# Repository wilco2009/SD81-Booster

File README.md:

# SD81 Booster — SD, sound, voice and memory interface for ZX81

An open hardware, open source project packing many features in a single interface.

## Credits

```
Hardware design & MCU firmware:  Alejandro Valero (wilco2009)
Z80 code / Modified ROM:         Pedro Gimeno (pgimeno)

Based on ZX81 ROM disassembly by Geoff Wearmouth
Preserved by Tomaž Šolc (https://www.tablix.org/~avian/spectrum/rom/)
```

## Features

- Load and save programs from/to a FAT32 microSD card in `.P` format, supporting common file and directory operations: list directory, copy/move/rename/delete files, change/create/remove directories.
- Up to 512 KB RAM, using a memory mapper in 8 KB blocks. There's also a simplified mode that allows up to 256 KB RAM, needing very simple paging code.
- The selected mapper page for any given block can be read back.
- Up to 128 user-defined characters. Compatible with the QuickSilva character definition mode — no longer restricted to the ROM's 64 characters and their inverses.
- AY-3-8910/12 sound chip emulation with `PLAY` command.
- AY VGM player, plays in background (does not support VGMs containing other chips than the AY).
- AY sound effects in background, via a programmable virtual machine (PEG).
- Speech synthesis based on the SP0256 chip (General Instrument), the same synthesiser used by the Currah MicroSpeech (ZX Spectrum) and The Voice (Videopac G7000/Odyssey 2). The `LOAD *SAY` command accepts English text directly.
- WAV audio file playback (uncompressed PCM).
- RGB colour video output, compatible with the Chroma81 interface standard.
- Real-time clock (RTC) with CR2032 backup battery.
- Programmable DB9 joystick port.
- Possibility to run code in the region between 32K and 48K (MC45 mode — see below).
- Minimal changes to the standard ROM. In particular, the ZX Printer and tape routines are preserved intact.

### What it doesn't do

- File names are restricted to characters supported by the ZX81 keyboard. The permitted characters for filenames are `A`–`Z`, `0`–`9`, `.`, `,`, `;`, `$`, `(`, `)`, `=`, `+`, `-`. The `/` character is the directory separator. Letters are treated as upper case when saving.
- AY sound chip emulation is not cycle-accurate.
- AY sound chip register access is not compatible with other interfaces.
- The memory mapping I/O port and layout are not compatible with other interfaces.
- There are no new BASIC keywords; most new functions are implemented through extensions to the `LOAD` and `SAVE` commands.

### Possible compatibility issues

- The SD81 Booster incorporates the functionality of the Chroma81 (RGB colour video) and QuickSilva (128 user-defined characters) interfaces. It is not designed to be used simultaneously with those physical interfaces connected at the same time.
- The memory area between 8 KB and 16 KB is no longer a mirror of the area between 0 and 8 KB.
- The same area is now read/write rather than read-only. If a program writes to used areas within that space, the expanded commands may crash and a hardware reset will be necessary.
- The ROM changes 8 bytes with respect to the original. Programs that depend on those specific bytes may fail (considered highly unlikely in practice).
- The memory mapper I/O port may clash with that of other interfaces.
- The general command interface I/O ports might clash with those of other interfaces.
- The USB-C port uses a CH340G chip for serial console output (115200-8N1). In Spectrum mode, port FBh is used, which is incompatible with the ZX Printer.

## MC45

MC45 (Machine Code in blocks 4 and 5) is a mode that allows any Z80 instruction — not just those with opcodes in the ranges 40h–7Fh and C0h–FFh — to run in the address range 8000h–BFFFh. The drawback is that the display file can no longer be in that area, so BASIC programs larger than 16 KB cannot be loaded or written while this mode is active.

The interface already includes a 33Ω protective resistor on the /HALT line internally. No modification to the ZX81 is required. There is no jumper to disable this feature on the current hardware version.

> **Note:** Some older documentation refers to a 680Ω resistor — that value applies to an alternative ZX81 hardware modification, not to the SD81 Booster itself.

## Getting started

The **SYS** folder must be present in the root of the microSD card — without it the interface will not start. It contains the ROM files required for operation.

See [MANUAL/ES/SD81_Manual_ES.md](MANUAL/ES/SD81_Manual_ES.md) for the full user manual in Spanish.

For the technical reference and MCU command descriptions, see the [DOC folder](DOC/).

## Firmware update

**Normal update (via SD bootloader):**
1. Copy the firmware `.bin` file (renamed as `firmware.bin`) to the root of the SD card.
2. Power on the ZX81. The bootloader detects the file, flashes it at `0x0800C000`, deletes it, and boots the application.

**Emergency recovery (via USB, for advanced users):**
1. Open the interface case and bridge the two upper pins of jumper **JP7** (on the component side, next to the USB-C port).
2. Connect the USB-C cable to a PC.
3. Use **STM32CubeProgrammer** to flash:
   - Bootloader at `0x08000000`
   - Application at `0x0800C000`

See [FIRMWARE/README_update.md](FIRMWARE/README_update.md) for detailed instructions.

## Building the ZX81 ROM

The ROM listing used here is the disassembly work of [Geoff Wearmouth](http://web.archive.org/web/20150815035607/http://www.wearmouth.demon.co.uk/zx81.htm), preserved by [Tomaž Šolc](https://www.tablix.org/~avian/spectrum/rom/).

The ROM can be built using [GNU binutils for Z80](https://github.com/atsidaev/binutils-z80), [Pasmo](https://pasmo.speccy.org/) or [MDL](https://github.com/santiontanon/mdlz80optimizer).

To build with GNU binutils:

    z80-unknown-coff-as sdmodrom.asm -o sdmodrom.o
    z80-unknown-coff-ld -Ttext 0 sdmodrom.o -o sdmodrom.bin

To build with Pasmo:

    pasmo sdmodrom.asm sdmodrom.bin

To build with MDL (dialects `pasmo` or `macro80`):

    java -jar mdl.jar -dialect macro80 -bin sdmodrom.bin sdmodrom.asm

## Games and game engines

Games and engines written for, or ported to, the SD81 Booster. Each one lives in its own repository:

- [Space Invaders](https://github.com/wilco2009/SD81Invaders): a replica of Taito's 1978 arcade, written from scratch in Z80 and tested on real hardware.
- [Manic Miner](https://codeberg.org/wilco2009/manicsd81): port of the ZX Spectrum classic (work in progress).
- [NanacoHell](https://codeberg.org/wilco2009/NANAKOHell_SD81Booster): port of the Spectrum 128K game, running in the Spectrum-compatible HiRes mode.
- [Mario](https://github.com/wilco2009/sd81mario): a Mario platformer.
- [ZXOilPanic](https://github.com/wilco2009/ZXOilPanic): a Game & Watch style oil-panic game, with an extra build target for the ZX81 + SD81 Booster.
- [SCUMM and AGI interpreters](https://github.com/wilco2009/SCUMM): interpreters running on the ZX81's Z80, for SCUMM v2 (Maniac Mansion, Zak McKracken) and Sierra's AGI (Space Quest I first).

The two-player network games (Connect 4, chess, Scrabble and the real-time sports games) are part of this repository, in [`EXAMPLES/NETGAME`](EXAMPLES/NETGAME).

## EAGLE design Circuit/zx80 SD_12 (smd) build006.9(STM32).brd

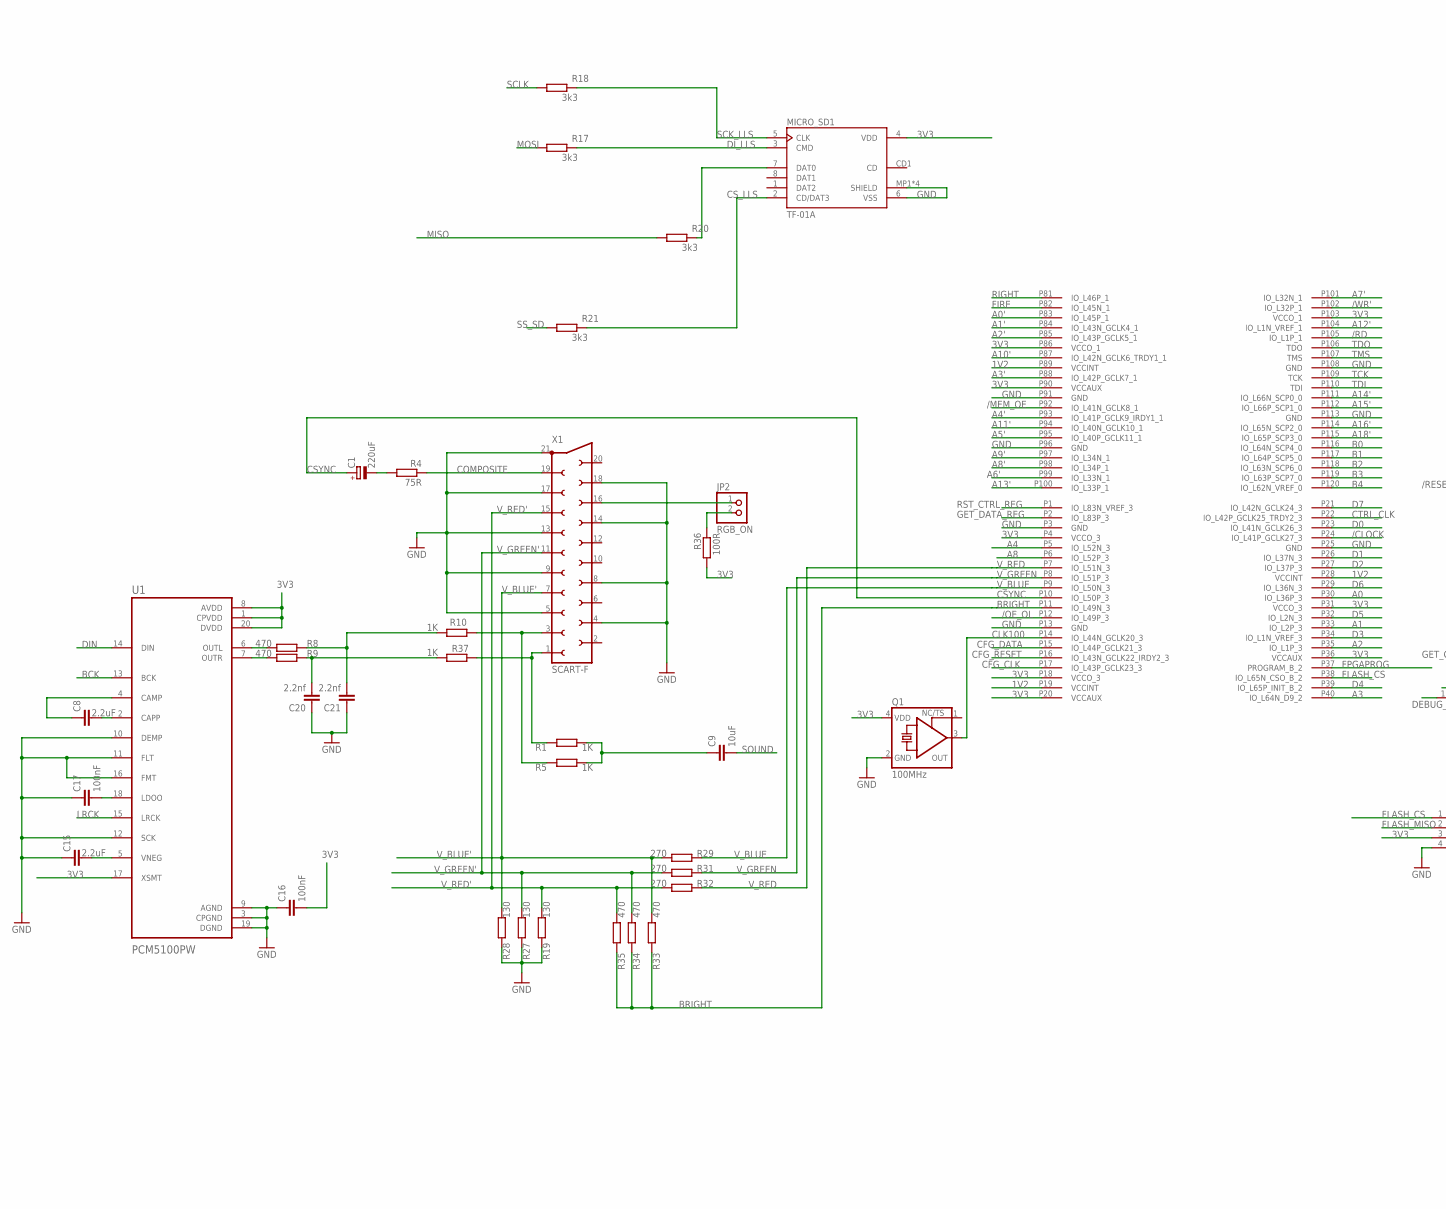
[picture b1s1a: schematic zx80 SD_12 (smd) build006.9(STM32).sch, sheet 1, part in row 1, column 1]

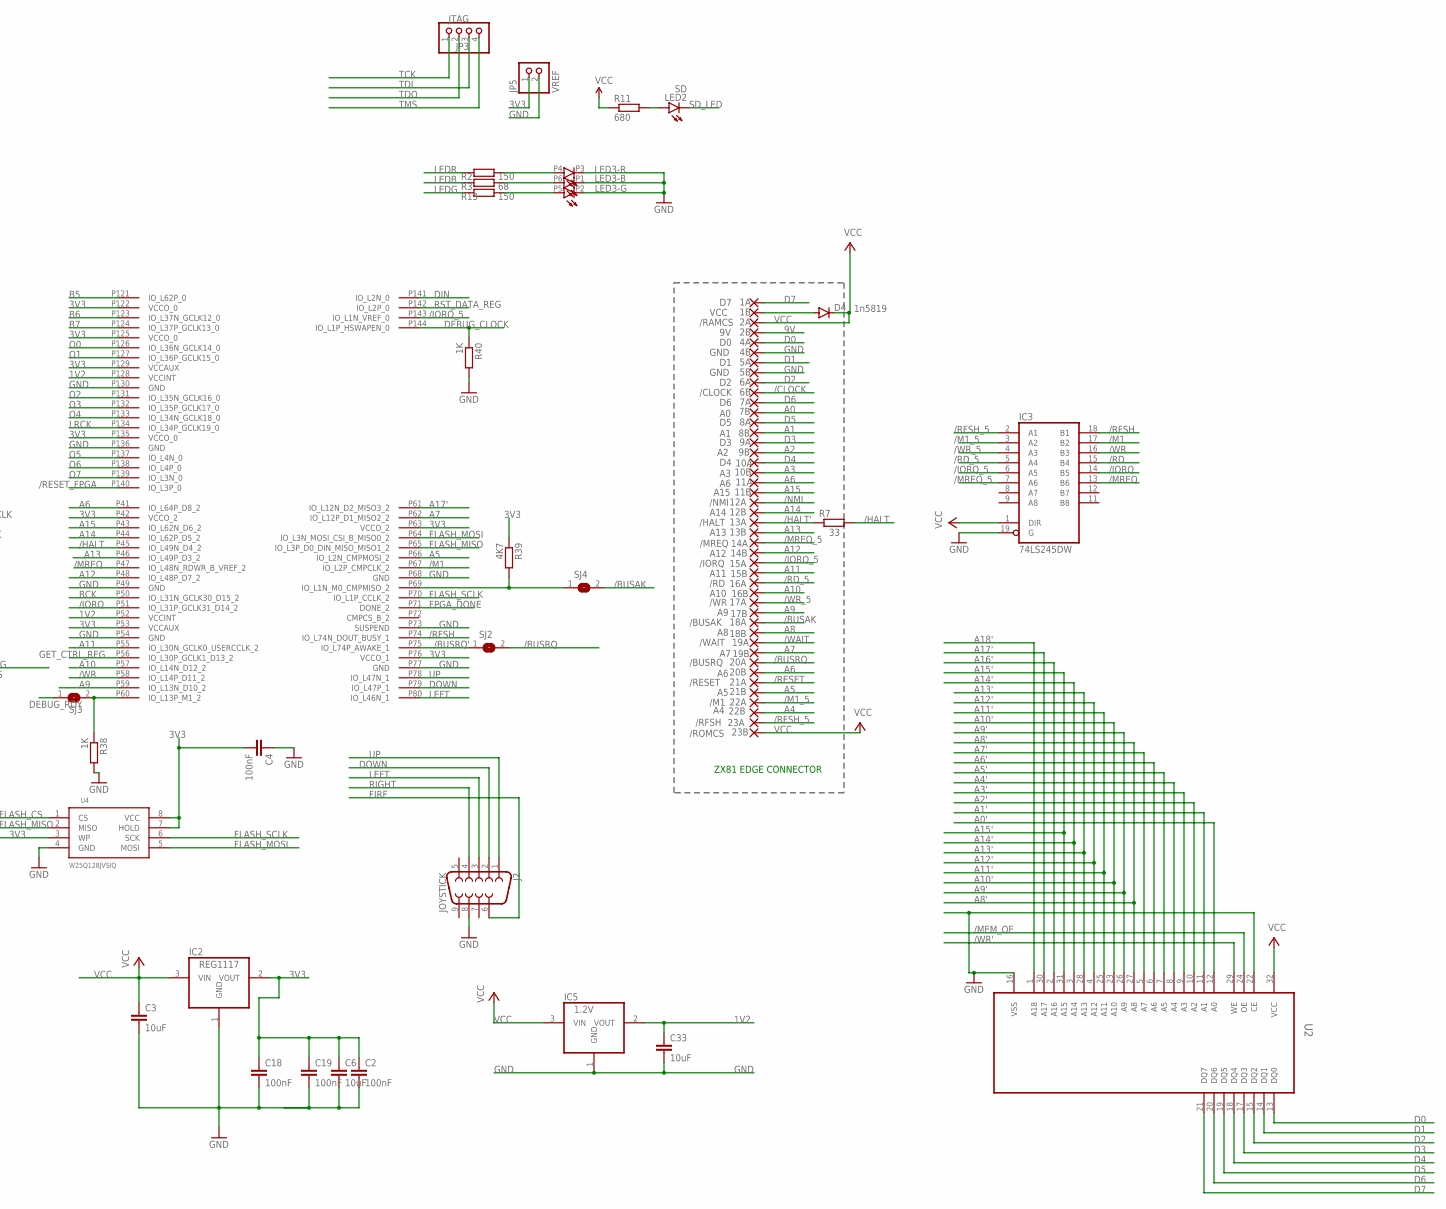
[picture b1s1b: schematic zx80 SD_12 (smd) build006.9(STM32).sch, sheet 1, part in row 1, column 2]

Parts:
1A: D7; EDGEPIN
1B: VCC; EDGEPIN
2A: /RAMCS; EDGEPIN
2B: 9V; EDGEPIN
4A: D0; EDGEPIN
4B, 5B: GND; EDGEPIN
5A: D1; EDGEPIN
6A: D2; EDGEPIN
6B: /CLOCK; EDGEPIN
7A: D6; EDGEPIN
7B: A0; EDGEPIN
8A: D5; EDGEPIN
8B: A1; EDGEPIN
9A: D3; EDGEPIN
9B: A2; EDGEPIN
10A: D4; EDGEPIN
10B: A3; EDGEPIN
11A, 20B: A6; EDGEPIN
11B: A15; EDGEPIN
12A: /NMI; EDGEPIN
12B: A14; EDGEPIN
13A: /HALT; EDGEPIN
13B: A13; EDGEPIN
14A: /MREQ; EDGEPIN
14B: A12; EDGEPIN
15A: /IORQ; EDGEPIN
15B: A11; EDGEPIN
16A: /RD; EDGEPIN
16B: A10; EDGEPIN
17A: /WR; EDGEPIN
17B: A9; EDGEPIN
18A: /BUSAK; EDGEPIN
18B: A8; EDGEPIN
19A: /WAIT; EDGEPIN
19B: A7; EDGEPIN
20A: /BUSRQ; EDGEPIN
21A: /RESET; EDGEPIN
21B: A5; EDGEPIN
22A: /M1; EDGEPIN
22B: A4; EDGEPIN
23A: /RFSH; EDGEPIN
23B: /ROMCS; EDGEPIN
C1: 220uF; UD-6,3X7,7_NICHICON
C2, C4, C16, C17, C18, C19: 100nF; C0402K
C3, C6, C9, C33: 10uF; C0402K
C8, C15: 2.2uF; C0402K
C20, C21: 2.2nf; C0603K
D4: 1n5819; SOD323-W
IC2: REG1117; SOT223
IC3: 74LS245DW; SO20W
IC5: 1.2V; SOT223
J2: JOYSTICK; DB9_MALE
JP2: RGB_ON; 1X02
JP3: JTAG; 1X04
JP5: VREF; 1X02
LED2: SD; CHIPLED_0805
LED3: STATUS; 3535-PLCC6
MICRO_SD1: TF-01A
Q1: 100MHz; 3.2X2.5_KXO-V96
R1, R5, R10, R37, R38, R40: 1K; R0402
R2, R13: 150; R0402
R3: 68; R0402
R4: 75R; R0402
R7: 33; R0402
R8, R9, R33, R34, R35: 470; R0402
R11: 680; R0402
R17, R18, R20, R21: 3k3; R0402
R19, R27, R28: 130; R0402
R29, R31, R32: 270; R0402
R36: 100R; R0402
R39: 4K7; R0402
SJ2, SJ3, SJ4: SJ
U1: PCM5100PW; SOP65P640X120-20N
U2: AS6C4008; SOP32-5
U4: W25Q128JVSIQ; SO08-EIAJ
U6: XC6SLX9-2TQG144C; TQ144
X1: SCART-F

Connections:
1V2: C33.1, IC5.2 (VOUT), U6.P19 (VCCINT), U6.P28 (VCCINT), U6.P52 (VCCINT), U6.P89 (VCCINT), U6.P128 (VCCINT)
3V3: C2.1, C4.2, C6.1, C16.2, C18.1, C19.1, IC2.2 (VOUT), JP5.1, MICRO_SD1.4 (VDD), Q1.4 (VDD), R36.2, R39.1, U1.1 (CPVDD), U1.8 (AVDD), U1.17 (XSMT), U1.20 (DVDD), U4.3 (WP), U4.7 (HOLD), U4.8 (VCC), U6.P4 (VCCO_3), U6.P18 (VCCO_3), U6.P20 (VCCAUX), U6.P31 (VCCO_3), U6.P36 (VCCAUX), U6.P42 (VCCO_2), U6.P53 (VCCAUX), U6.P63 (VCCO_2), U6.P76 (VCCO_1), U6.P86 (VCCO_1), U6.P90 (VCCAUX), U6.P103 (VCCO_1), U6.P122 (VCCO_0), U6.P125 (VCCO_0), U6.P129 (VCCAUX), U6.P135 (VCCO_0); also elsewhere on the board
9V: 2B.1
/BUSAK: 18A.1, SJ4.2
/BUSRQ: 20A.1, SJ2.2
/BUSRQ': SJ2.1, U6.P75 (IO_L74P_AWAKE_1)
/CLOCK: 6B.1, U6.P24 (IO_L41P_GCLK27_3)
/HALT: R7.2, U6.P45 (IO_L49N_D4_2)
/HALT': 13A.1, R7.1
/IORQ: IC3.14 (B5), U6.P51 (IO_L31P_GCLK31_D14_2)
/IORQ_5: 15A.1, IC3.6 (A5), U6.P143 (IO_L1N_VREF_0)
/M1: IC3.17 (B2), U6.P67 (IO_L2P_CMPCLK_2)
/M1_5: 22A.1, IC3.3 (A2)
/MEM_OE: U2.24 (OE), U6.P92 (IO_L41N_GCLK8_1); also elsewhere on the board
/MREQ: IC3.13 (B6), U6.P47 (IO_L48N_RDWR_B_VREF_2)
/MREQ_5: 14A.1, IC3.7 (A6)
/NMI: 12A.1
/OE_OL: U6.P12 (IO_L49P_3); also elsewhere on the board
/RD: IC3.15 (B4), U6.P105 (IO_L1P_1)
/RD_5: 16A.1, IC3.5 (A4)
/RESET: 21A.1; also elsewhere on the board
/RESET_FPGA: U6.P140 (IO_L3P_0); also elsewhere on the board
/RFSH: IC3.18 (B1), U6.P74 (IO_L74N_DOUT_BUSY_1)
/RFSH_5: 23A.1, IC3.2 (A1)
/WAIT: 19A.1; also elsewhere on the board
/WR: IC3.16 (B3), U6.P58 (IO_L14P_D11_2)
/WR': U2.29 (WE), U6.P102 (IO_L32P_1); also elsewhere on the board
/WR_5: 17A.1, IC3.4 (A3)
A0: 7B.1, U6.P30 (IO_L36P_3)
A0': U2.12 (A0), U6.P83 (IO_L45P_1); also elsewhere on the board
A1: 8B.1, U6.P33 (IO_L2P_3)
A1': U2.11 (A1), U6.P84 (IO_L43N_GCLK4_1); also elsewhere on the board
A2: 9B.1, U6.P35 (IO_L1P_3)
A2': U2.10 (A2), U6.P85 (IO_L43P_GCLK5_1); also elsewhere on the board
A3: 10B.1, U6.P40 (IO_L64N_D9_2)
A3': U2.9 (A3), U6.P88 (IO_L42P_GCLK7_1); also elsewhere on the board
A4: 22B.1, U6.P5 (IO_L52N_3)
A4': U2.8 (A4), U6.P93 (IO_L41P_GCLK9_IRDY1_1); also elsewhere on the board
A5: 21B.1, U6.P66 (IO_L2N_CMPMOSI_2)
A5': U2.7 (A5), U6.P95 (IO_L40P_GCLK11_1); also elsewhere on the board
A6: 11A.1, 20B.1, U6.P41 (IO_L64P_D8_2)
A6': U2.6 (A6), U6.P99 (IO_L33N_1); also elsewhere on the board
A7: 19B.1, U6.P62 (IO_L12P_D1_MISO2_2)
A7': U2.5 (A7), U6.P101 (IO_L32N_1); also elsewhere on the board
A8: 18B.1, U6.P6 (IO_L52P_3)
A8': U2.27 (A8), U6.P98 (IO_L34P_1); also elsewhere on the board
A9: 17B.1, U6.P59 (IO_L13N_D10_2)
A9': U2.26 (A9), U6.P97 (IO_L34N_1); also elsewhere on the board
A10: 16B.1, U6.P57 (IO_L14N_D12_2)
A10': U2.23 (A10), U6.P87 (IO_L42N_GCLK6_TRDY1_1); also elsewhere on the board
A11: 15B.1, U6.P55 (IO_L30N_GCLK0_USERCCLK_2)
A11': U2.25 (A11), U6.P94 (IO_L40N_GCLK10_1); also elsewhere on the board
A12: 14B.1, U6.P48 (IO_L48P_D7_2)
A12': U2.4 (A12), U6.P104 (IO_L1N_VREF_1); also elsewhere on the board
A13: 13B.1, U6.P46 (IO_L49P_D3_2)
A13': U2.28 (A13), U6.P100 (IO_L33P_1); also elsewhere on the board
A14: 12B.1, U6.P44 (IO_L62P_D5_2)
A14': U2.3 (A14), U6.P111 (IO_L66N_SCP0_0); also elsewhere on the board
A15: 11B.1, U6.P43 (IO_L62N_D6_2)
A15': U2.31 (A15), U6.P112 (IO_L66P_SCP1_0); also elsewhere on the board
A16': U2.2 (A16), U6.P114 (IO_L65N_SCP2_0); also elsewhere on the board
A17': U2.30 (A17), U6.P61 (IO_L12N_D2_MISO3_2); also elsewhere on the board
A18': U2.1 (A18), U6.P115 (IO_L65P_SCP3_0); also elsewhere on the board
B0: U6.P116 (IO_L64N_SCP4_0); also elsewhere on the board
B1: U6.P117 (IO_L64P_SCP5_0); also elsewhere on the board
B2: U6.P118 (IO_L63N_SCP6_0); also elsewhere on the board
B3: U6.P119 (IO_L63P_SCP7_0); also elsewhere on the board
B4: U6.P120 (IO_L62N_VREF_0); also elsewhere on the board
B5: U6.P121 (IO_L62P_0); also elsewhere on the board
B6: U6.P123 (IO_L37N_GCLK12_0); also elsewhere on the board
B7: U6.P124 (IO_L37P_GCLK13_0); also elsewhere on the board
BCK: U1.13 (BCK), U6.P50 (IO_L31N_GCLK30_D15_2)
BRIGHT: R33.1, R34.1, R35.1, U6.P11 (IO_L49N_3)
CFG_CLK: U6.P17 (IO_L43P_GCLK23_3); also elsewhere on the board
CFG_DATA: U6.P15 (IO_L44P_GCLK21_3); also elsewhere on the board
CFG_RESET: U6.P16 (IO_L43N_GCLK22_IRDY2_3); also elsewhere on the board
CLK100: Q1.3 (OUT), U6.P14 (IO_L44N_GCLK20_3)
COMPOSITE: R4.1, X1.19
CSYNC: C1.+, U6.P10 (IO_L50P_3)
CS_LLS: MICRO_SD1.2 (CD/DAT3), R21.2
CTRL_CLK: U6.P22 (IO_L42P_GCLK25_TRDY2_3); also elsewhere on the board
D0: 4A.1, U2.13 (DQ0), U6.P23 (IO_L41N_GCLK26_3)
D1: 5A.1, U2.14 (DQ1), U6.P26 (IO_L37N_3)
D2: 6A.1, U2.15 (DQ2), U6.P27 (IO_L37P_3)
D3: 9A.1, U2.17 (DQ3), U6.P34 (IO_L1N_VREF_3)
D4: 10A.1, U2.18 (DQ4), U6.P39 (IO_L65P_INIT_B_2)
D5: 8A.1, U2.19 (DQ5), U6.P32 (IO_L2N_3)
D6: 7A.1, U2.20 (DQ6), U6.P29 (IO_L36N_3)
D7: 1A.1, U2.21 (DQ7), U6.P21 (IO_L42N_GCLK24_3)
DEBUG_CLOCK: R40.1, U6.P144 (IO_L1P_HSWAPEN_0); also elsewhere on the board
DEBUG_RDY: SJ3.1; also elsewhere on the board
DIN: U1.14 (DIN), U6.P141 (IO_L2N_0)
DI_LLS: MICRO_SD1.3 (CMD), R17.2
DOWN: J2.2, U6.P79 (IO_L47P_1)
FIRE: J2.6, U6.P82 (IO_L45N_1)
FLASH_CS: U4.1 (CS), U6.P38 (IO_L65N_CSO_B_2); also elsewhere on the board
FLASH_MISO: U4.2 (MISO), U6.P65 (IO_L3P_D0_DIN_MISO_MISO1_2); also elsewhere on the board
FLASH_MOSI: U4.5 (MOSI), U6.P64 (IO_L3N_MOSI_CSI_B_MISO0_2); also elsewhere on the board
FLASH_SCLK: U4.6 (SCK), U6.P70 (IO_L1P_CCLK_2); also elsewhere on the board
FPGAPROG: U6.P37 (PROGRAM_B_2); also elsewhere on the board
FPGA_DONE: U6.P71 (DONE_2); also elsewhere on the board
GET_CTRL_REG: U6.P56 (IO_L30P_GCLK1_D13_2); also elsewhere on the board
GET_DATA_REG: U6.P2 (IO_L83P_3); also elsewhere on the board
GND: 4B.1, 5B.1, C2.2, C3.2, C4.1, C6.2, C15.1, C16.1, C17.1, C18.2, C19.2, C20.1, C21.1, C33.2, IC2.1 (GND), IC3.10 (GND), IC3.19 (G), IC5.1 (GND), J2.8, JP5.2, LED3.P1 (C), LED3.P2 (C), LED3.P3 (C), MICRO_SD1.6 (VSS), MICRO_SD1.MP1 (SHIELD), MICRO_SD1.MP2 (SHIELD), MICRO_SD1.MP3 (SHIELD), MICRO_SD1.MP4 (SHIELD), Q1.2 (GND), R19.2, R27.2, R28.2, R38.2, R40.2, U1.3 (CPGND), U1.9 (AGND), U1.10 (DEMP), U1.11 (FLT), U1.12 (SCK), U1.16 (FMT), U1.19 (DGND), U2.16 (VSS), U2.22 (CE), U4.4 (GND), U6.P3 (GND), U6.P13 (GND), U6.P25 (GND), U6.P49 (GND), U6.P54 (GND), U6.P68 (GND), U6.P73 (SUSPEND), U6.P77 (GND), U6.P91 (GND), U6.P96 (GND), U6.P108 (GND), U6.P113 (GND), U6.P130 (GND), U6.P136 (GND), X1.4, X1.5, X1.8, X1.9, X1.13, X1.14, X1.17, X1.18, X1.21; also elsewhere on the board
LEDB: R3.1; also elsewhere on the board
LEDG: R13.1; also elsewhere on the board
LEDR: R2.1; also elsewhere on the board
LEFT: J2.3, U6.P80 (IO_L46N_1)
LRCK: U1.15 (LRCK), U6.P134 (IO_L34P_GCLK19_0)
MISO: R20.1; also elsewhere on the board
MOSI: R17.1; also elsewhere on the board
unnamed: R39.2, SJ4.1, U6.P69 (IO_L1N_M0_CMPMISO_2)
unnamed: MICRO_SD1.7 (DAT0), R20.2
unnamed: 1B.1, D4.A
unnamed: C1.-, R4.2
unnamed: R5.1, R10.2, X1.3
unnamed: C9.1, R1.2, R5.2
unnamed: C21.2, R8.1, R10.1
unnamed: LED2.A, R11.2
unnamed: JP2.1, X1.16
unnamed: C20.2, R9.1, R37.1
unnamed: LED3.P4 (A), R2.2
unnamed: LED3.P6 (A), R3.2
unnamed: LED3.P5 (A), R13.2
unnamed: JP2.2, R36.1
unnamed: R38.1, SJ3.2, U6.P60 (IO_L13P_M1_2)
unnamed: R8.2, U1.6 (OUTL)
unnamed: R9.2, U1.7 (OUTR)
unnamed: C8.2, U1.2 (CAPP)
unnamed: C8.1, U1.4 (CAMP)
unnamed: C15.2, U1.5 (VNEG)
unnamed: C17.2, U1.18 (LDOO)
unnamed: R1.1, R37.2, X1.1
O0: U6.P126 (IO_L36N_GCLK14_0); also elsewhere on the board
O1: U6.P127 (IO_L36P_GCLK15_0); also elsewhere on the board
O2: U6.P131 (IO_L35N_GCLK16_0); also elsewhere on the board
O3: U6.P132 (IO_L35P_GCLK17_0); also elsewhere on the board
O4: U6.P133 (IO_L34N_GCLK18_0); also elsewhere on the board
O5: U6.P137 (IO_L4N_0); also elsewhere on the board
O6: U6.P138 (IO_L4P_0); also elsewhere on the board
O7: U6.P139 (IO_L3N_0); also elsewhere on the board
RIGHT: J2.4, U6.P81 (IO_L46P_1)
RST_CTRL_REG: U6.P1 (IO_L83N_VREF_3); also elsewhere on the board
RST_DATA_REG: U6.P142 (IO_L2P_0); also elsewhere on the board
SCK_LLS: MICRO_SD1.5 (CLK), R18.2
SCLK: R18.1; also elsewhere on the board
SD_LED: LED2.C; also elsewhere on the board
SOUND: C9.2; also elsewhere on the board
SS_SD: R21.1; also elsewhere on the board
TCK: JP3.1, U6.P109 (TCK)
TDI: JP3.3, U6.P110 (TDI)
TDO: JP3.2, U6.P106 (TDO)
TMS: JP3.4, U6.P107 (TMS)
UP: J2.1, U6.P78 (IO_L47N_1)
VCC: 2A.1, 23B.1, C3.1, D4.C, IC2.3 (VIN), IC3.1 (DIR), IC3.20 (VCC), IC5.3 (VIN), R11.1, U2.32 (VCC); also elsewhere on the board
V_BLUE: R29.1, U6.P9 (IO_L50N_3)
V_BLUE': R28.1, R29.2, R33.2, X1.7
V_GREEN: R31.1, U6.P8 (IO_L51P_3)
V_GREEN': R27.1, R31.2, R34.2, X1.11
V_RED: R32.1, U6.P7 (IO_L51N_3)
V_RED': R19.1, R32.2, R35.2, X1.15

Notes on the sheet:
ZX81 EDGE CONNECTOR

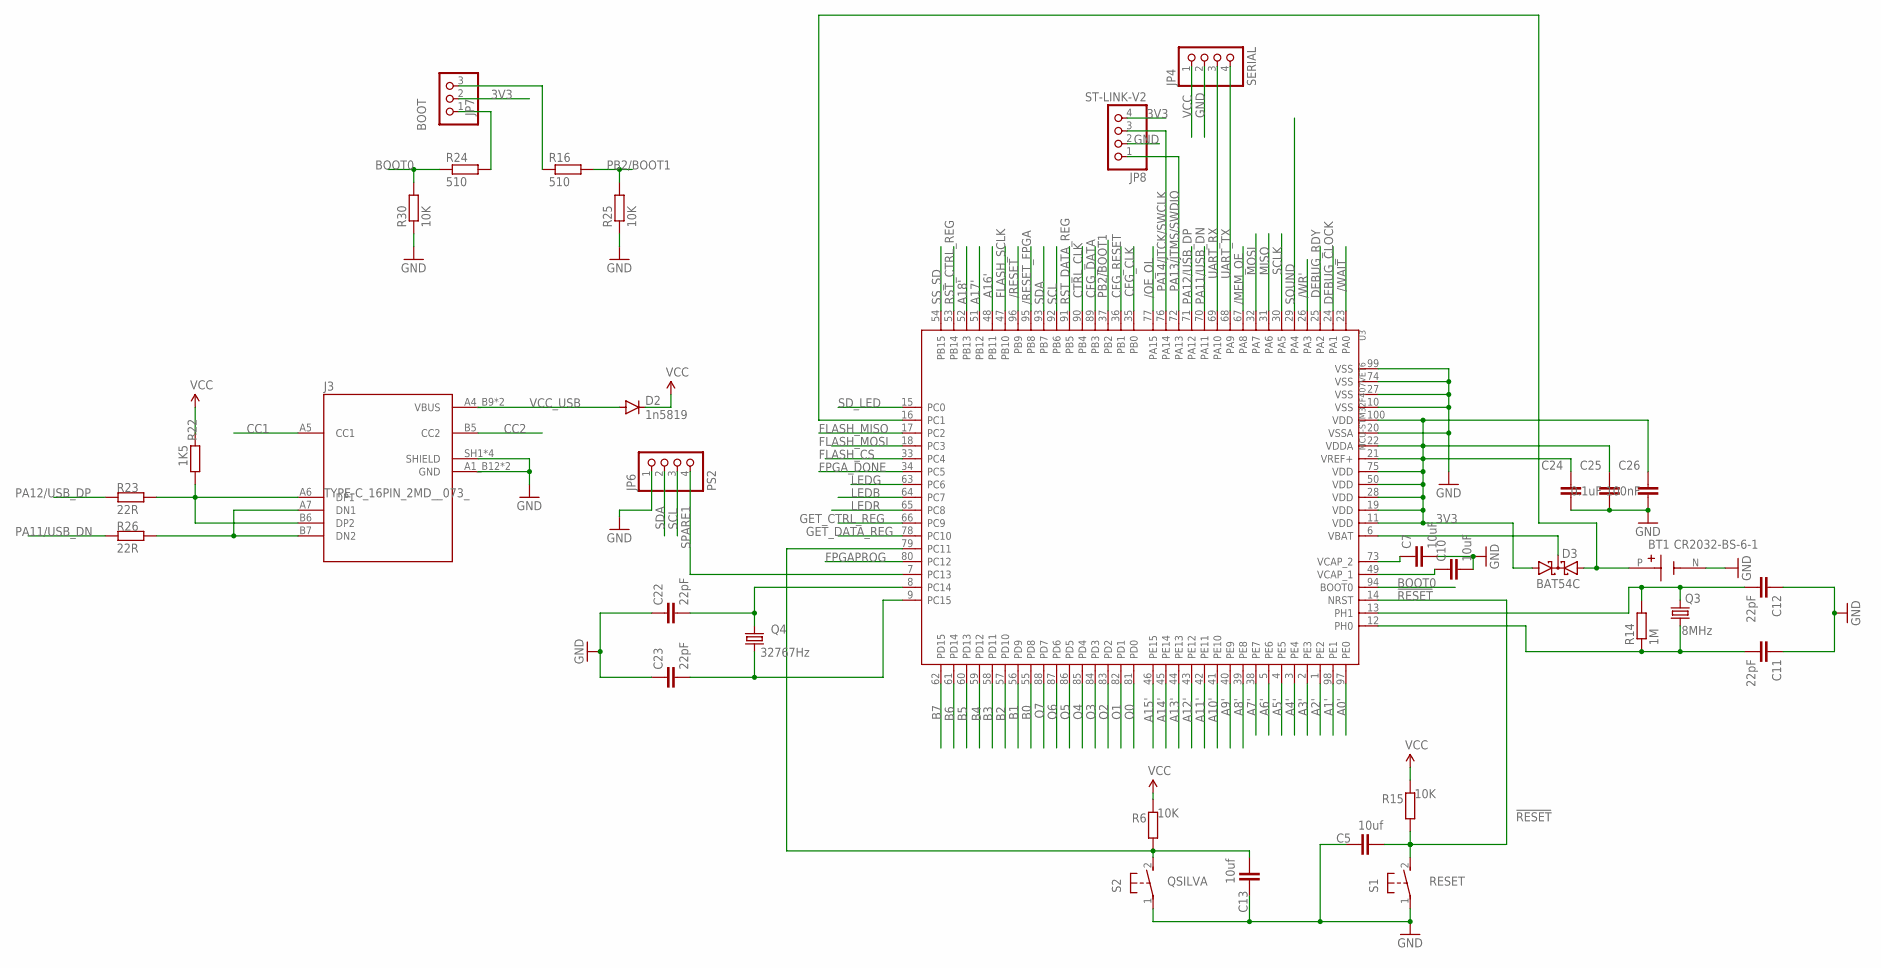
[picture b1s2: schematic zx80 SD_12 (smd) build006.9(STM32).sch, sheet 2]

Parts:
BT1: CR2032-BS-6-1; BAT_CR2032-BS-6-1
C5, C13: 10uf; C0402K
C7, C10: 10uF; C0402K
C11, C12, C22, C23: 22pF; C0603
C24, C25: 0.1uF; C0402K
C26: 100nF; C0402K
D2: 1n5819; SOD323-W
D3: BAT54C; SOT23
J3: TYPE-C_16PIN_2MD__073_; SHOUHAN_TYPE-C_16PIN_2MD__073_
JP4: SERIAL; 1X04
JP6: PS2; 1X04
JP7: BOOT; 1X03
JP8: ST-LINK-V2; 1X04
Q3: 8MHz; 3.2X2.5_KX-7
Q4: 32767Hz; 3.2X1.5
R6, R15, R25, R30: 10K; R0402
R14: 1M; R0402
R16, R24: 510; R0402
R22: 1K5; R0402
R23, R26: 22R; R0402
S1: RESET; B3F-31XX
S2: QSILVA; B3F-31XX
U3: MCU-STM32F407VET6; LQFP100-0.5-13.8X13.8MM

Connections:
3V3: C24.1, C25.1, C26.1, D3.1 (A1), JP7.2, JP8.4, U3.11 (VDD), U3.19 (VDD), U3.21 (VREF+), U3.22 (VDDA), U3.28 (VDD), U3.50 (VDD), U3.75 (VDD), U3.100 (VDD); also elsewhere on the board
!RESET: C5.2, R15.1, S1.2 (S), U3.14 (NRST)
/MEM_OE: U3.67 (PA8); also elsewhere on the board
/OE_OL: U3.77 (PA15); also elsewhere on the board
/RESET: U3.96 (PB9); also elsewhere on the board
/RESET_FPGA: U3.95 (PB8); also elsewhere on the board
/WAIT: U3.23 (PA0); also elsewhere on the board
/WR': U3.26 (PA3); also elsewhere on the board
A0': U3.97 (PE0); also elsewhere on the board
A1': U3.98 (PE1); also elsewhere on the board
A2': U3.1 (PE2); also elsewhere on the board
A3': U3.2 (PE3); also elsewhere on the board
A4': U3.3 (PE4); also elsewhere on the board
A5': U3.4 (PE5); also elsewhere on the board
A6': U3.5 (PE6); also elsewhere on the board
A7': U3.38 (PE7); also elsewhere on the board
A8': U3.39 (PE8); also elsewhere on the board
A9': U3.40 (PE9); also elsewhere on the board
A10': U3.41 (PE10); also elsewhere on the board
A11': U3.42 (PE11); also elsewhere on the board
A12': U3.43 (PE12); also elsewhere on the board
A13': U3.44 (PE13); also elsewhere on the board
A14': U3.45 (PE14); also elsewhere on the board
A15': U3.46 (PE15); also elsewhere on the board
A16': U3.48 (PB11); also elsewhere on the board
A17': U3.51 (PB12); also elsewhere on the board
A18': U3.52 (PB13); also elsewhere on the board
B0: U3.55 (PD8); also elsewhere on the board
B1: U3.56 (PD9); also elsewhere on the board
B2: U3.57 (PD10); also elsewhere on the board
B3: U3.58 (PD11); also elsewhere on the board
B4: U3.59 (PD12); also elsewhere on the board
B5: U3.60 (PD13); also elsewhere on the board
B6: U3.61 (PD14); also elsewhere on the board
B7: U3.62 (PD15); also elsewhere on the board
BAT: BT1.P (POS), D3.2 (A2), U3.16 (PC1)
BOOT0: R24.1, R30.2, U3.94 (BOOT0)
CC1: J3.A5 (CC1)
CC2: J3.B5 (CC2)
CFG_CLK: U3.35 (PB0); also elsewhere on the board
CFG_DATA: U3.89 (PB3); also elsewhere on the board
CFG_RESET: U3.36 (PB1); also elsewhere on the board
CTRL_CLK: U3.90 (PB4); also elsewhere on the board
DEBUG_CLOCK: U3.24 (PA1); also elsewhere on the board
DEBUG_RDY: U3.25 (PA2); also elsewhere on the board
FLASH_CS: U3.33 (PC4); also elsewhere on the board
FLASH_MISO: U3.17 (PC2); also elsewhere on the board
FLASH_MOSI: U3.18 (PC3); also elsewhere on the board
FLASH_SCLK: U3.47 (PB10); also elsewhere on the board
FPGAPROG: U3.80 (PC12); also elsewhere on the board
FPGA_DONE: U3.34 (PC5); also elsewhere on the board
GET_CTRL_REG: U3.66 (PC9); also elsewhere on the board
GET_DATA_REG: U3.78 (PC10); also elsewhere on the board
GND: BT1.N (NEG), C5.1, C7.2, C10.2, C11.1, C12.1, C13.1, C22.1, C23.1, C24.2, C25.2, C26.2, J3.A1_B12 (GND), J3.B1_A12 (GND), J3.SH1 (SHIELD), J3.SH2 (SHIELD), J3.SH3 (SHIELD), J3.SH4 (SHIELD), JP4.2, JP6.1, JP8.2, R25.1, R30.1, S1.1, S2.1, U3.10 (VSS), U3.20 (VSSA), U3.27 (VSS), U3.74 (VSS), U3.99 (VSS); also elsewhere on the board
LEDB: U3.64 (PC7); also elsewhere on the board
LEDG: U3.63 (PC6); also elsewhere on the board
LEDR: U3.65 (PC8); also elsewhere on the board
MISO: U3.31 (PA6); also elsewhere on the board
MOSI: U3.32 (PA7); also elsewhere on the board
unnamed: J3.A6 (DP1), J3.B6 (DP2), R22.1, R23.1
unnamed: D3.3 (CC), U3.6 (VBAT)
unnamed: C13.2, R6.1, S2.2 (S), U3.79 (PC11)
unnamed: C7.1, U3.73 (VCAP_2)
unnamed: J3.A7 (DN1), J3.B7 (DN2), R26.1
unnamed: C10.1, U3.49 (VCAP_1)
unnamed: C11.2, Q3.1, R14.1, U3.12 (PH0)
unnamed: C12.2, Q3.3 (2), R14.2, U3.13 (PH1)
unnamed: JP7.3, R16.1
unnamed: JP7.1, R24.2
unnamed: C22.2, Q4.2, U3.8 (PC14)
unnamed: C23.2, Q4.1, U3.9 (PC15)
O0: U3.81 (PD0); also elsewhere on the board
O1: U3.82 (PD1); also elsewhere on the board
O2: U3.83 (PD2); also elsewhere on the board
O3: U3.84 (PD3); also elsewhere on the board
O4: U3.85 (PD4); also elsewhere on the board
O5: U3.86 (PD5); also elsewhere on the board
O6: U3.87 (PD6); also elsewhere on the board
O7: U3.88 (PD7); also elsewhere on the board
PA11/USB_DN: R26.2, U3.70 (PA11)
PA12/USB_DP: R23.2, U3.71 (PA12)
PA13/JTMS/SWDIO: JP8.1, U3.72 (PA13)
PA14/JTCK/SWCLK: JP8.3, U3.76 (PA14)
PB2/BOOT1: R16.2, R25.2, U3.37 (PB2)
RST_CTRL_REG: U3.53 (PB14); also elsewhere on the board
RST_DATA_REG: U3.91 (PB5); also elsewhere on the board
SCL: JP6.3, U3.92 (PB6)
SCLK: U3.30 (PA5); also elsewhere on the board
SDA: JP6.2, U3.93 (PB7)
SD_LED: U3.15 (PC0); also elsewhere on the board
SOUND: U3.29 (PA4); also elsewhere on the board
SPARE1: JP6.4, U3.7 (PC13)
SS_SD: U3.54 (PB15); also elsewhere on the board
UART_RX: JP4.3, U3.69 (PA10)
UART_TX: JP4.4, U3.68 (PA9)
VCC: D2.C, JP4.1, R6.2, R15.2, R22.2; also elsewhere on the board
VCC_USB: D2.A, J3.A4_B9 (VBUS), J3.B4_A9 (VBUS)

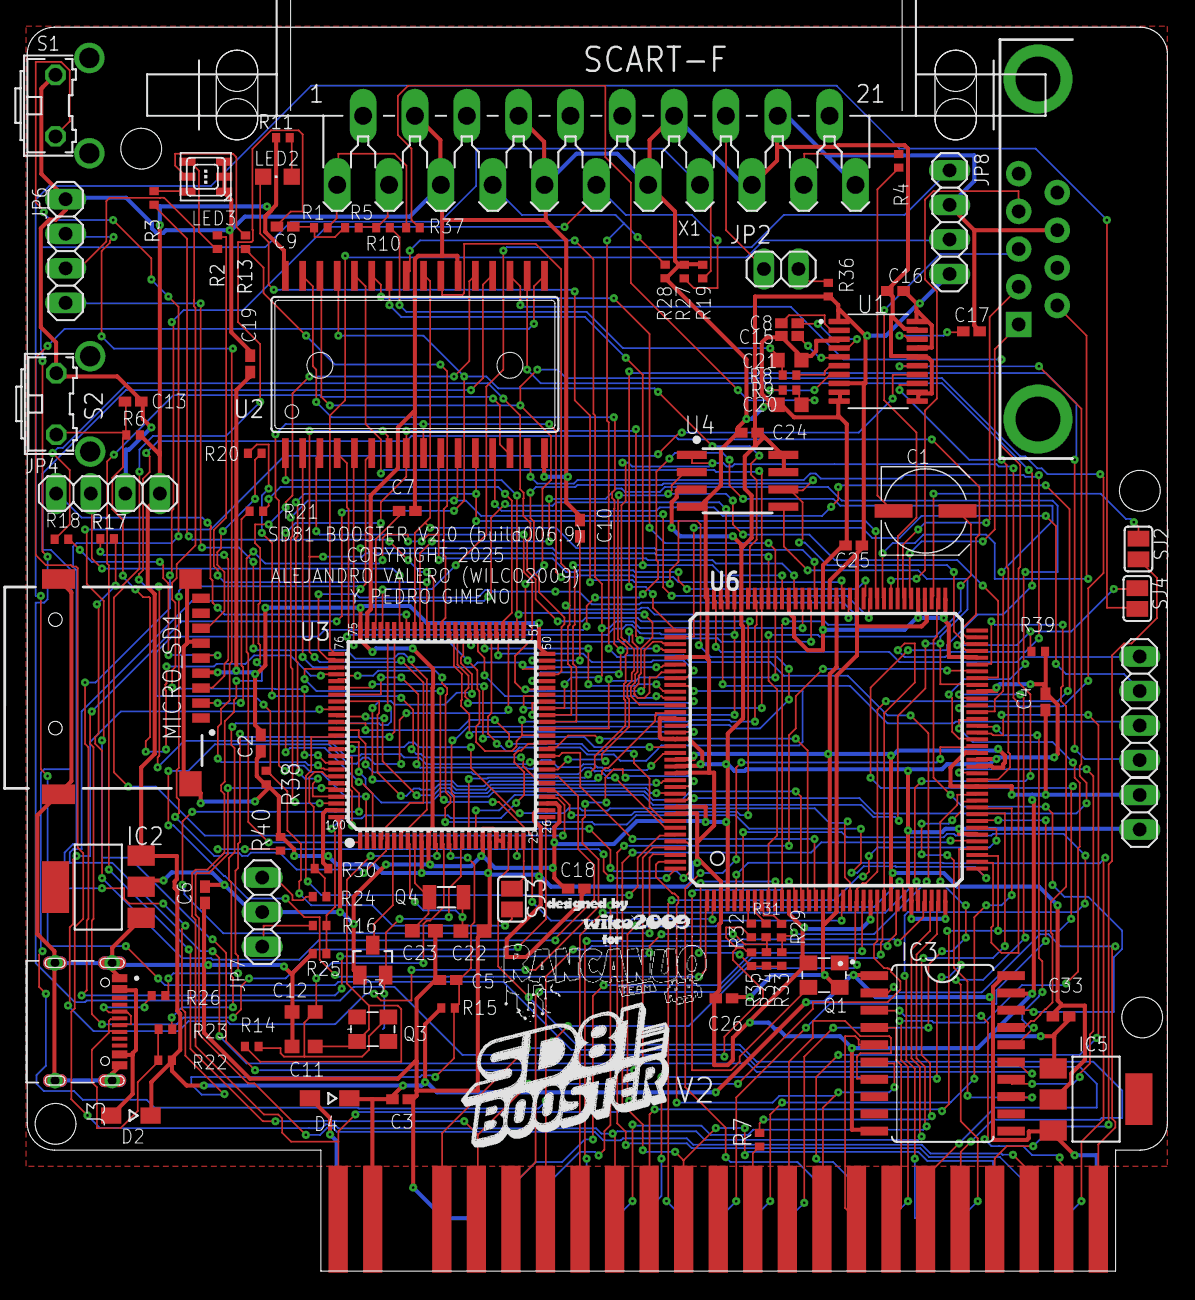
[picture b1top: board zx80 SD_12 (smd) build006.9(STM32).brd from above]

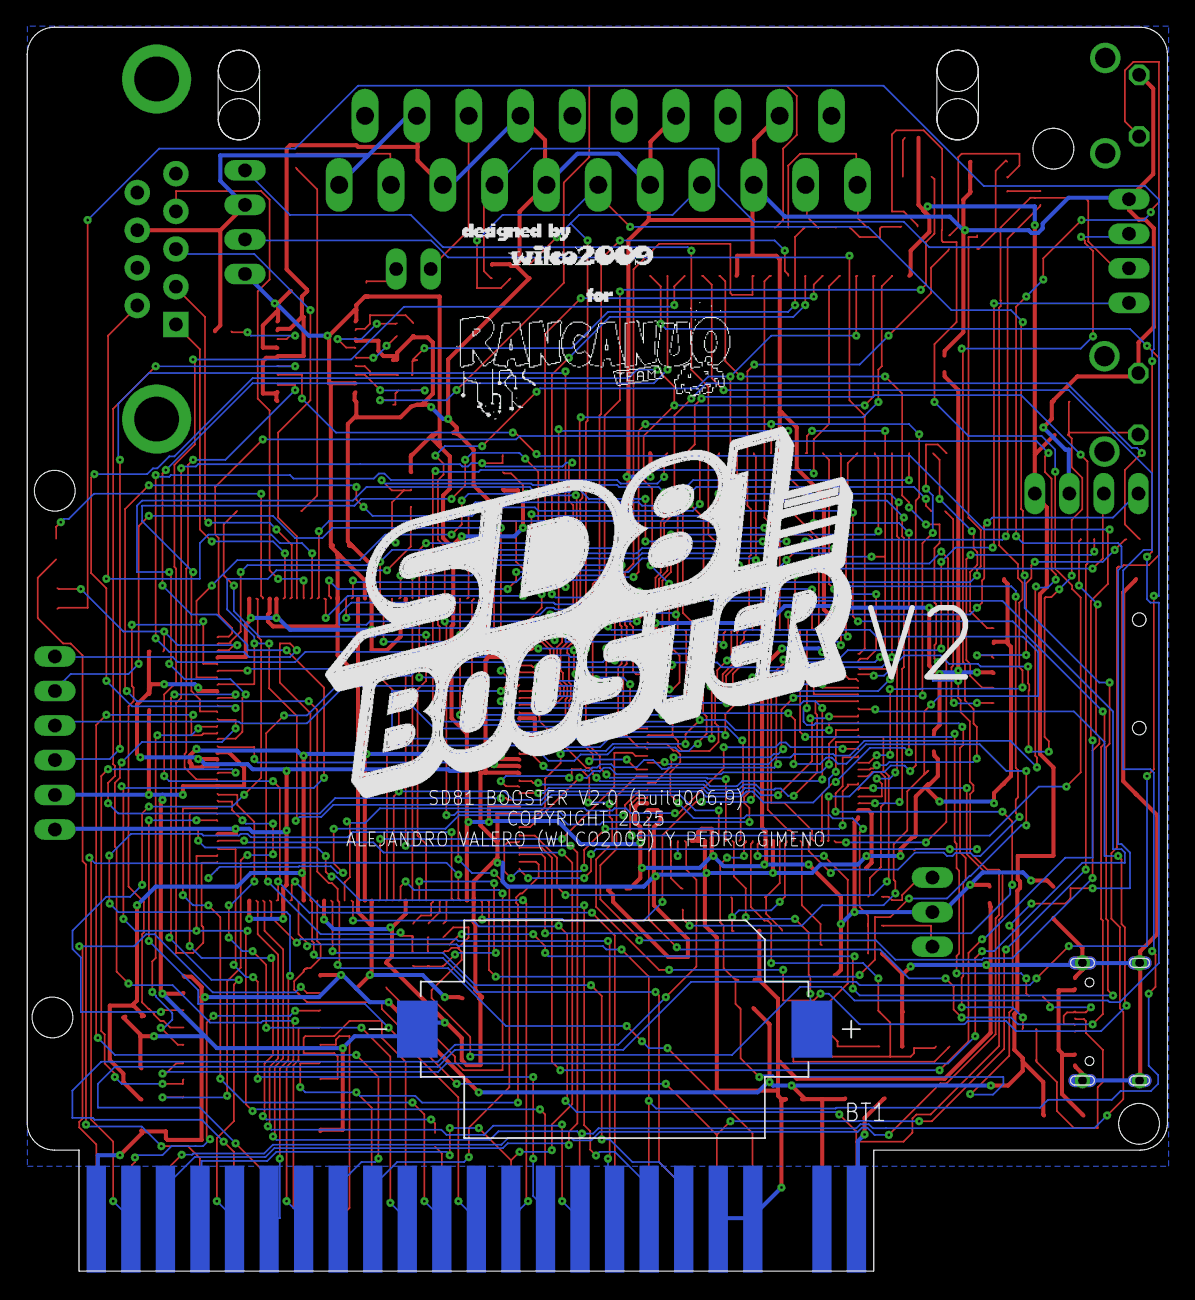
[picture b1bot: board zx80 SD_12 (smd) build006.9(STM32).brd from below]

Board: 2 copper layers, 83.8 x 91.4 mm, 142 parts (23 on the bottom side), 185 nets.

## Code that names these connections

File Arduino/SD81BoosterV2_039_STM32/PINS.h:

#define nWAIT           PA0
#define DEBUG_CLOCK     PA1
#define DEBUG_RDY       PA2
#define nWRb            PA3
#define DAC_PIN         PA4       // Pin PA4 para la salida DAC
#define SCLK            PA5
#define MISO            PA6
#define MOSI            PA7
#define nMEM_OEb        PA8
#define UART_TX         PA9
#define UART_RX         PA10
#define USB_DN          PA11
#define USB_DP          PA12
#define SWDIO           PA13
#define SWCLK           PA  14
#define nOE_OL          PA15

#define CFG_CLK         PB0
#define CFG_RESET       PB1
#define BOOT1           PB2
#define CFG_DATA        PB3
#define CTRL_CLK        PB4
#define RST_DATA_REG    PB5
#define FPGA_HSWAPEN    PB5
#define SCL             PB6   // unconnected
#define SDA             PB7   
#define WAIT_SERIAL     PB7   
#define FPGA_RESET      PB8
#define Z80_RESET       PB9
#define FLASH_SCLK      PB10
#define A16b            PB11 
#define A17b            PB12 
#define A18b            PB13 
#define RST_CTRL_REG    PB14
#define SS_SD           PB15  

#define SD_LED          PC0
#define VBAT_IN         PC1    // only as reference. see VBAT.cpp
#define FLASH_MISO      PC2
#define FLASH_MOSI      PC3
#define FLASH_CS        PC4
#define FPGA_DONE       PC5
#define ST_LED_G        PC6
#define ST_LED_B        PC7
#define ST_LED_R        PC8
#define GET_CTRL_REG    PC9
#define GET_DATA_REG    PC10
#define QSPIN           PC11     
#define FPGAPROG        PC12
#define SPARE           PC13
#define CLK_32KH_0      PC14
#define CLK_32KH_1      PC15

#define ioLatch         GPIOD // shared
#define Data            GPIOD // shared

#define Addr            GPIOE
#define A0b             PE0
#define A1b             PE1
#define A2b             PE2
#define A3b             PE3
#define A4b             PE4
#define A5b             PE5
#define A6b             PE6
#define A7b             PE7
#define A8b             PE8
#define A9b             PE9
#define A10b            PE10
#define A11b            PE11
#define A12b            PE12
#define A13b            PE13
#define A14b            PE14
#define A15b            PE15

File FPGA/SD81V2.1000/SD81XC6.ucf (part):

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
NET "nRST_CTRL_REG" LOC = P1;
//
NET "GET_DATA_REG" LOC = P2;
// NET "GND"  			LOC = "P3"  ; 				//
// NET "3V3"  			LOC = "P4"  ; 				//
//
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//
NET "VBLUE" LOC = P9;
//
NET "CSYNC" LOC = P10;
//
NET "BRIGHT" LOC = P11;
//
NET "nOE_OL" LOC = P12;
// NET "GND"  			LOC = "P13" ; 				//
//
NET "CLK100" LOC = P14;
NET "CFG_DATA" LOC = P15;
//
NET "CFG_RESET" LOC = P16;
//
NET "CFG_CLK" LOC = P17;
// NET "3V3"  			LOC = "P18" ; 				//
// NET "1V2"  			LOC = "P19" ; 				//
// NET "3V3"  			LOC = "P20" ; 				//
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NET "D7" LOC = P21;
//
//NET "PAL_NTSC" LOC = P22;
NET "CTRL_CLK" LOC = P22;
//
NET "D0" LOC = P23 ;
//
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NET "A2" LOC = P35;
// NET "3V3"  			LOC = "P36" ; 				//
// NET "PROGRAM B2"	LOC = "P37" ; 				//
// NET "FLASH_CS"  		LOC = "P38" ; 				//
//
NET "D4" LOC = P39;
//
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NET "A12" LOC = P48;
// NET "GND"  			LOC = "P49" ; 				//
//
NET "BCK" LOC = P50;
// 
NET "nIORQ" LOC = P51;
// NET "1V2"  			LOC = "P52" ; 				//
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//
NET "A11" LOC = P55;
//
NET "GET_CTRL_REG" LOC = P56;
//
NET "A10" LOC = P57;
//
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//
NET "A9" LOC = P59;
//
NET "DEBUG_RDY" LOC = P60;
//
NET "A17x" LOC = P61;
//
NET "A7" LOC = P62;
// NET "3V3"  			LOC = "P63" ; 				//
//NET "FLASH_MOSI"  	LOC = "P64" ; 				//
//NET "FLASH_MISO"  	LOC = "P65" ; 				//
//
NET "A5" LOC = P66;
//
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// NET "GND"  			LOC = "P68" ; 				//
//
NET "nBUSAK" LOC = P69;
//NET "FLASH_SCLK"  	LOC = "P70" ; 				//
//NET "DONE"  		LOC = "P71" ; 				//
// NET "CMPCS_B"		LOC = "P72" ; 				//
// NET "GND"  			LOC = "P73" ; 				//
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//
NET "RIGHT" LOC = P81;
//
NET "FIRE" LOC = P82;
//
NET "A0x" LOC = P83;
//
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//
NET "O4" LOC = P133;
//
NET "LRCK" LOC = P134;
// NET "3V3"  			LOC = "P135"; 				//
// NET "GND"  			LOC = "P136"; 				//
//
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NET "O7" LOC = P139;
NET "nRESET" LOC = P140;
//
NET "DIN" LOC = P141;
//
NET "nRST_DATA_REG" LOC = P142;
//
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#NET "B5" DRIVE = 12;
#NET "B6" DRIVE = 12;
#NET "B7" DRIVE = 12;
#NET "BRIGHT" DRIVE = 12;
#NET "CFG_CLK" DRIVE = 12;
#NET "CFG_DATA" DRIVE = 12;
#NET "CFG_RESET" DRIVE = 12;
#NET "CSYNC" DRIVE = 12;
#NET "CTRL_CLK" DRIVE = 12;
#NET "D0" DRIVE = 12;
#NET "D1" DRIVE = 12;
#NET "D2" DRIVE = 12;
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#NET "D6" DRIVE = 12;
#NET "D7" DRIVE = 12;
#NET "DOWN" DRIVE = 12;
#NET "FIRE" DRIVE = 12;
#NET "FULL_PAGING" DRIVE = 12;
#NET "GET_CTRL_REG" DRIVE = 12;
#NET "GET_DATA_REG" DRIVE = 12;
#NET "LEFT" DRIVE = 12;
#NET "nCLOCK" DRIVE = 12;
#NET "nHALT" DRIVE = 12;
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#NET "O6" DRIVE = 12;
#NET "O7" DRIVE = 12;
#//NET "PAL_NTSC" DRIVE = 12;
#NET "BCK" DRIVE = 12;
#NET "LRCK" DRIVE = 12;
#NET "DIN" DRIVE = 12;
#NET "RIGHT" DRIVE = 12;
#NET "nMEM_OEm" DRIVE = 12;
#NET "SEL_128CHARS" DRIVE = 12;
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
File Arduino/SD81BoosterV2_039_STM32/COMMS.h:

#ifndef COMMS_H
#define COMMS_H
#include <stdint.h>

#define CMD_BITS 4

void write_LATCH_O(uint8_t d);
uint8_t read_LATCH_B(void);
void idle_tasks();
void set_clock(bool c);
void reset_commands();
void ToggleClock();
uint8_t GetByteFromZ80();
void SendByteToZ80(uint8_t byte);
uint8_t GetByteFromZ80_IT();
void SendByteToZ80_IT(uint8_t byte);
void _rst_ctrl_reg(uint8_t status);
void _rst_data_reg(uint8_t status);
void get_ctrl_reg(void);
void get_data_reg(void);
void read_data();
void jmpfar();

#define cfgcmd_JOYSTICK   0
#define cfgcmd_MC45       1
#define cfgcmd_MODE48K    2
#define cfgcmd_QSEN       3
#define cfgcmd_FULLPAG    4
#define cfgcmd_128CHARS   5
#define cfgcmd_256CHARS   6
#define cfgcmd_ROMLOCK    7
#define cfgcmd_DBGPAUSE   8   // depurador: pausa (la FPGA reacciona al cambio)
#define cfgcmd_DBGLOADED  9   // depurador: monitor cargado en la pagina 63 (y armado)
#define cfgcmd_DBGPOKE    10  // depurador: el monitor escribe como el programa (POKEs y BRAM)
#define cfgcmd_DBGDIRTY   11  // depurador: borrar las paginas escritas (1 y despues 0)
#define cfgcmd_DBGTRACE   12  // depurador: la traza de la FPGA (historial, sim_int 0.13)
#define cfgcmd_KEYS       13  // teclado virtual: una fila de la matriz (vkeys.v), 3 bits de fila y 5 de columnas
#define cfgcmd_MOUSE_A    14  // raton: x, y, botones, rueda (mouse_regs.v; el Z80 lo lee por el indice 20 de $3FEF)
#define cfgcmd_MOUSE_B    15  // raton: rawx, rawy, seq, conectado


void send_debug_params(uint16_t pixel_cnt, uint16_t line_cnt);
void send_config(void);
bool send_joycfg(char* config);// UP DOWN LEFT RIGHT FIRE
void send_bit_config(uint8_t command, uint8_t value);
// Teclado virtual: la matriz de 8 filas x 5 columnas que se "pulsa" desde fuera (la web del depurador).
// Solo se manda a la FPGA lo que cambia; si nadie lo refresca en 1,5 s, se suelta todo
void vkeys_set(const uint8_t* rows);
void vkeys_poll(void);
void vkeys_clear(void);
// Raton: si ha cambiado algo (MOUSE.cpp), lo manda a la FPGA (como mucho cada 8 ms). Se llama desde idle_tasks()
void mouse_fpga_poll(void);
void rst_config(void);
uint8_t cfg_value(uint8_t command);   // ultimo valor mandado con send_bit_config

const int OUTPUT_LATCH[] = {PD0, PD1, PD2, PD3, PD4, PD5, PD6, PD7}; 
const int INPUT_LATCH[] = {PD8, PD9, PD10, PD11, PD12, PD13, PD14, PD15}; 

extern uint8_t joy_cfg[5][2];

#endif

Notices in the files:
Circuit/zx80 SD_12 (smd) build006.9(STM32).brd:
COPYRIGHT 2025
parts and their libraries:
crystal-geyer_V1_0: Copyright: Geyer-Electronic
SparkFun-Connectors: Licensing: Creative Commons ShareAlike 4.0 International - https://creativecommons.org/licenses/by-sa/4.0
